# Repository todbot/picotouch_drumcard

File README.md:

# picotouch_drumcard

Playing card-sized (2.5"x3.5") sequencer / synth / USB / MIDI touch controller

Successor to the [picotouch_bizcard MIDI controller](https://github.com/todbot/picotouch_bizcard)

## Features

* 17 capacitive touch pads arranged in a step-sequencer layout
* 15 reverse-mounted LEDs as status / touch indicators
* TRS-A MIDI In and Out
* Audio out (via 12-bit PWM)
* Battery powered, with lipo battery charging circuit
* Powered by Raspberry Pi Pico board
* Programmable with CircuitPython, Arduino, etc.

# Example code

* Drum sequencer + synth
* MIDI controller
* Macropad
* USB-MIDI interface

# 

https://github.com/user-attachments/assets/234cb804-bad1-4454-a92b-b1dc36a663cc

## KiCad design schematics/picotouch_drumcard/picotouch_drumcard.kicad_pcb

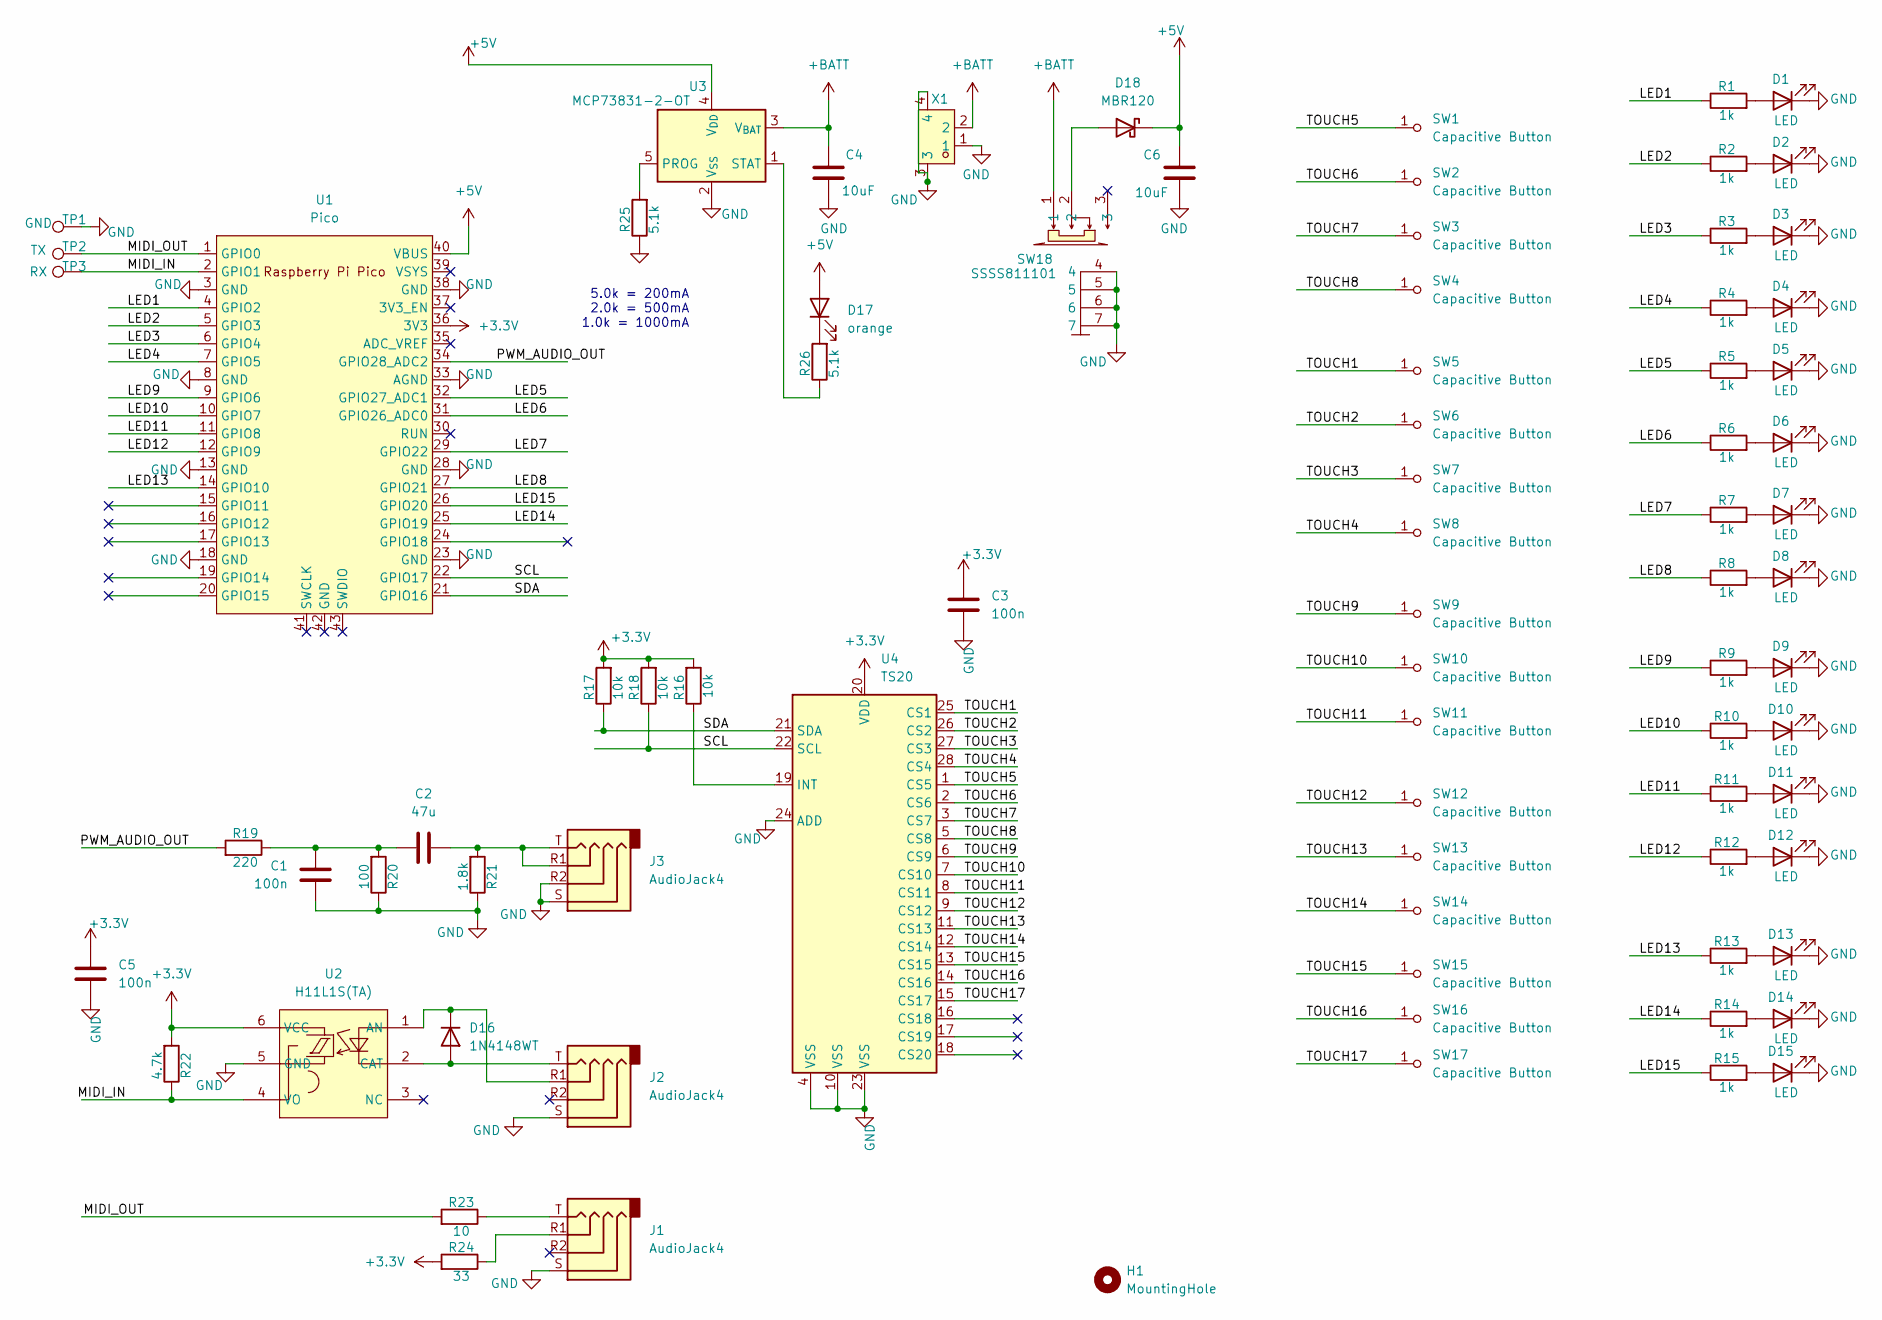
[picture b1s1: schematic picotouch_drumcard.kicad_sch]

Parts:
C1, C3, C5: 100n; C_0603_1608Metric
C2: 47u; C_0603_1608Metric
C4, C6: 10uF; C_0603_1608Metric
D1, D2, D3, D4, D5, D6, D7, D8, D9, D10, D11, D12, D13, D14, D15: LED; LED1206_LTST-C230KRKT-cutout; LCSC C125107
D16: 1N4148WT; D_SOD-123F; LCSC Part C64898
D17: orange; LED_0603_1608Metric
D18: MBR120; D_SOD-123F; LCSC Part C130880
H1: MountingHole; MountingHole_2.5mm
J1: AudioJack4; Jack_3.5mm_PJ320D_Horizontal; LCSC C431535
J2, J3: AudioJack4; Jack_3.5mm_PJ320D_Horizontal; LCSC Part C431535
R1, R2, R3, R4, R5, R6, R7, R8, R9, R10, R11, R12, R13, R14, R15: 1k; R_0603_1608Metric
R16, R17, R18: 10k; R_0603_1608Metric
R19: 220; R_0603_1608Metric
R20: 100; R_0603_1608Metric
R21: 1.8k; R_0603_1608Metric
R22: 4.7k; R_0603_1608Metric
R23: 10; R_0603_1608Metric
R24: 33; R_0603_1608Metric
R25, R26: 5.1k; R_0603_1608Metric
SW1, SW2, SW3, SW4, SW5, SW6, SW7, SW8, SW9, SW10, SW11: Capacitive Button; Pad-CapacitiveTouch
SW12, SW13, SW14, SW15, SW16, SW17: Capacitive Button; Pad-CapacitiveTouch-SparkFun-10x5mm-roundrect
SW18: SSSS811101; SW-SMD_SSSS811101; LCSC Part C109335
TP1: GND; TestPoint_Pad_D2.0mm
TP2: TX; TestPoint_Pad_D2.0mm
TP3: RX; TestPoint_Pad_D2.0mm
U1: Pico; RPi_Pico_SMD
U2: H11L1S(TA); SMD-6_L7.3-W6.5-P2.54-LS10.2-BL; LCSC Part C78589
U3: MCP73831-2-OT; SOT-23-5; LCSC Part C424093
U4: TS20; TSSOP-28_4.4x9.7mm_P0.65mm; LCSC Part C95876
X1: AFC20-S02ACA-00; CONN-SMD_AFC20-S02ACA-00; LCSC Part C2764211

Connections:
+3.3V: C3.1, C5.1, R16.2, R17.2, R18.2, R22.2, R24.2, U1.36 (3V3), U2.6 (VCC), U4.20 (VDD)
+5V: C6.1, D17.2 (A), D18.1 (K), U1.40 (VBUS), U3.4 (V_{DD})
+BATT: C4.1, SW18.1, U3.3 (V_{BAT}), X1.2
/LED1: R1.1, U1.4 (GPIO2)
/LED2: R2.1, U1.5 (GPIO3)
/LED3: R3.1, U1.6 (GPIO4)
/LED4: R4.1, U1.7 (GPIO5)
/LED5: R5.1, U1.32 (GPIO27_ADC1)
/LED6: R6.1, U1.31 (GPIO26_ADC0)
/LED7: R7.1, U1.29 (GPIO22)
/LED8: R8.1, U1.27 (GPIO21)
/LED9: R9.1, U1.9 (GPIO6)
/LED10: R10.1, U1.10 (GPIO7)
/LED11: R11.1, U1.11 (GPIO8)
/LED12: R12.1, U1.12 (GPIO9)
/LED13: R13.1, U1.14 (GPIO10)
/LED14: R14.1, U1.25 (GPIO19)
/LED15: R15.1, U1.26 (GPIO20)
/MIDI_IN: R22.1, TP3.1, U1.2 (GPIO1), U2.4 (VO)
/MIDI_OUT: R23.2, TP2.1, U1.1 (GPIO0)
/PWM_AUDIO_OUT: R19.2, U1.34 (GPIO28_ADC2)
/SCL: R18.1, U1.22 (GPIO17), U4.22 (SCL)
/SDA: R17.1, U1.21 (GPIO16), U4.21 (SDA)
/TOUCH1: SW5.1 (A), U4.25 (CS1)
/TOUCH2: SW6.1 (A), U4.26 (CS2)
/TOUCH3: SW7.1 (A), U4.27 (CS3)
/TOUCH4: SW8.1 (A), U4.28 (CS4)
/TOUCH5: SW1.1 (A), U4.1 (CS5)
/TOUCH6: SW2.1 (A), U4.2 (CS6)
/TOUCH7: SW3.1 (A), U4.3 (CS7)
/TOUCH8: SW4.1 (A), U4.5 (CS8)
/TOUCH9: SW9.1 (A), U4.6 (CS9)
/TOUCH10: SW10.1 (A), U4.7 (CS10)
/TOUCH11: SW11.1 (A), U4.8 (CS11)
/TOUCH12: SW12.1 (A), U4.9 (CS12)
/TOUCH13: SW13.1 (A), U4.11 (CS13)
/TOUCH14: SW14.1 (A), U4.12 (CS14)
/TOUCH15: SW15.1 (A), U4.13 (CS15)
/TOUCH16: SW16.1 (A), U4.14 (CS16)
/TOUCH17: SW17.1 (A), U4.15 (CS17)
GND: C1.2, C3.2, C4.2, C5.2, C6.2, D1.1 (K), D2.1 (K), D3.1 (K), D4.1 (K), D5.1 (K), D6.1 (K), D7.1 (K), D8.1 (K), D9.1 (K), D10.1 (K), D11.1 (K), D12.1 (K), D13.1 (K), D14.1 (K), D15.1 (K), J1.S, J2.S, J3.R2, J3.S, R20.1, R21.1, R25.1, SW18.4, SW18.5, SW18.6, SW18.7, TP1.1, U1.3 (GND), U1.8 (GND), U1.13 (GND), U1.18 (GND), U1.23 (GND), U1.28 (GND), U1.33 (AGND), U1.38 (GND), U2.5 (GND), U3.2 (V_{SS}), U4.4 (VSS), U4.10 (VSS), U4.23 (VSS), U4.24 (ADD), X1.1, X1.3, X1.4
unnamed: C1.1, C2.2, R19.1, R20.2
unnamed: C2.1, J3.R1, J3.T, R21.2
unnamed: D1.2 (A), R1.2
unnamed: D2.2 (A), R2.2
unnamed: D3.2 (A), R3.2
unnamed: D4.2 (A), R4.2
unnamed: D5.2 (A), R5.2
unnamed: D6.2 (A), R6.2
unnamed: D7.2 (A), R7.2
unnamed: D8.2 (A), R8.2
unnamed: D9.2 (A), R9.2
unnamed: D10.2 (A), R10.2
unnamed: D11.2 (A), R11.2
unnamed: D12.2 (A), R12.2
unnamed: D13.2 (A), R13.2
unnamed: D14.2 (A), R14.2
unnamed: D15.2 (A), R15.2
unnamed: D16.2 (A), J2.T, U2.2 (CAT)
unnamed: D16.1 (K), J2.R1, U2.1 (AN)
unnamed: D17.1 (K), R26.2
unnamed: D18.2 (A), SW18.2
unnamed: J1.R1, R24.1
unnamed: J1.T, R23.1
unnamed: R25.2, U3.5 (PROG)
unnamed: R26.1, U3.1 (STAT)
unnamed: R16.1, U4.19 (INT)

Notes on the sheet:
5.0k = 200mA 2.0k = 500mA 1.0k = 1000mA

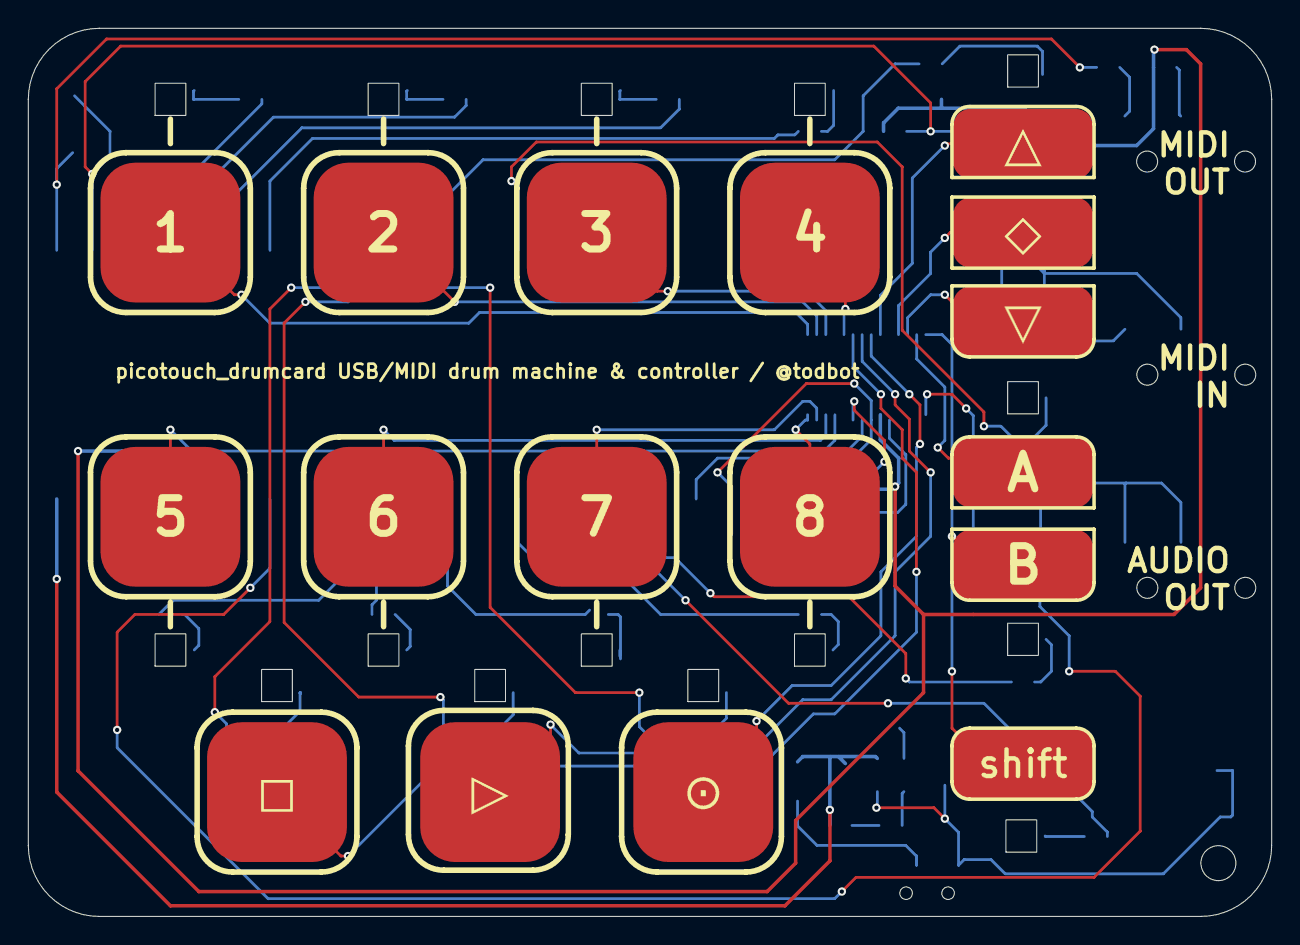
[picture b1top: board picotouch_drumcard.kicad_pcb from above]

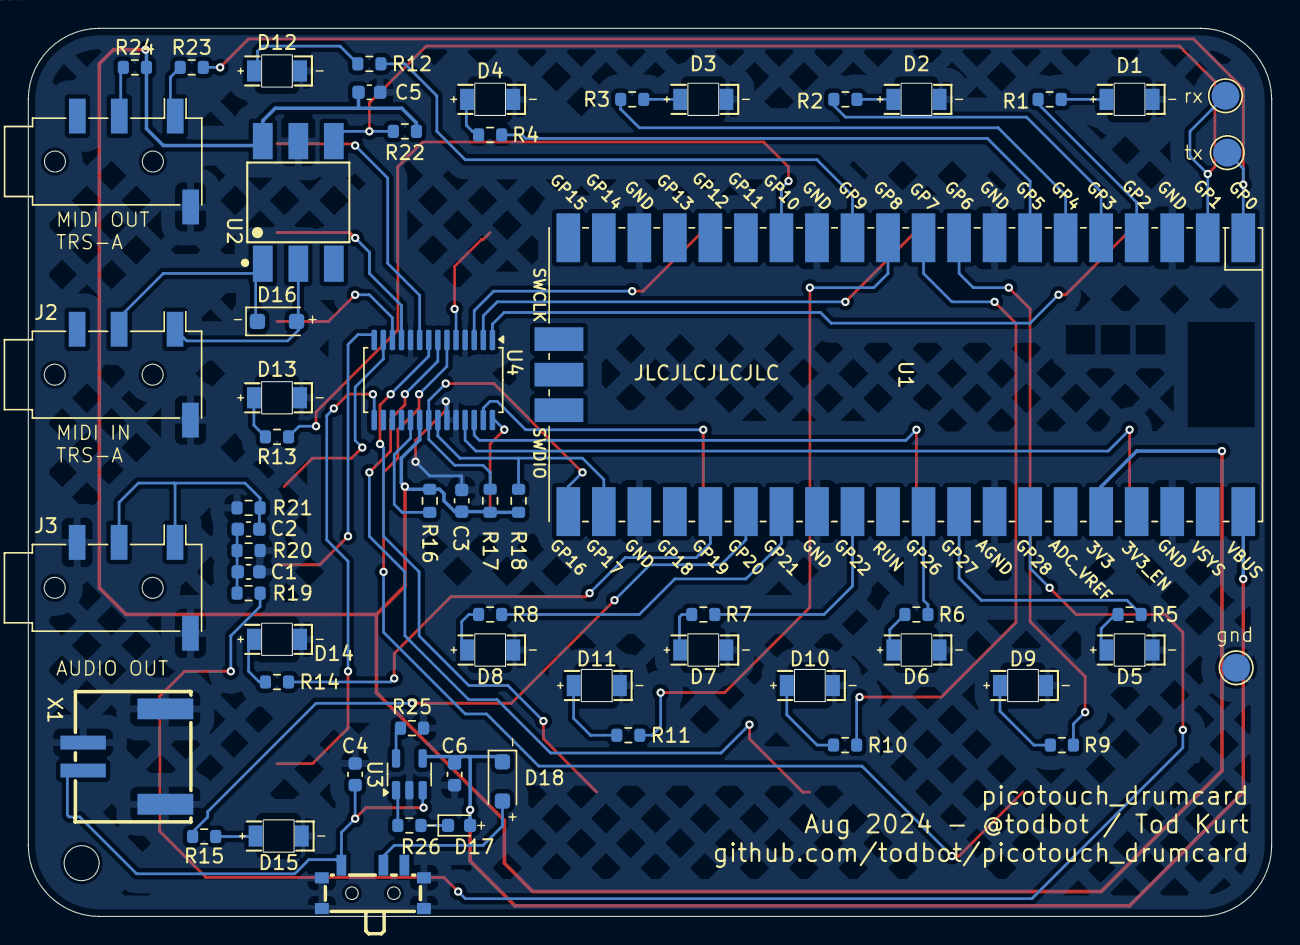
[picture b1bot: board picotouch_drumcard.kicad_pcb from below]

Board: 2 copper layers, 88.9 x 63.5 mm, 80 parts (62 on the bottom side), 67 nets.

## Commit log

2024-08-01 first
2024-08-01 second
2024-08-01 added protection diodes
2024-08-01 fix button labels
2024-08-02 tuning layout
2024-08-02 add missing cap on opto
2024-08-02 sent files to production
2024-08-02 untested hwtest
2024-08-02 dangit forgot power switch
2024-08-02 add missing cap to charger circuit, nudge around charger to fit
2024-08-05 cleanup
2024-08-05 add 3d printable enclosure and CAD files
2024-08-07 hwtest with actual hardware
2024-08-10 sigh more fixes to charging circuit
2024-08-10 audio out needs Ring2 to Gnd for headphones to work (I knew this)
2024-08-13 hwtest sends midi on both uart & usb
2024-08-14 add oct up/down to hwtest
2024-08-16 somewhat working drum machine
2024-08-16 add kit selection
2024-08-16 make default drum patterns a little better
